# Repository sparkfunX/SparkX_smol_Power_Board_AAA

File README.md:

# SparkX smôl Power Board : AAA

[*SparkX smôl Power Board : AAA (SPX-18621)*](https://www.sparkfun.com/products/18621)

A power board for smôl:
- JST battery connector
- Boost converter
- Power can be provided by one or two AAA or AA batteries
- ATtiny43 for intelligent power management

## Repository Contents

- **/Documentation** - Datasheets etc.
- **/Hardware** - Eagle design files
- **LICENSE.md** contains the licence information

## Product Versions

- [SPX-18621](https://www.sparkfun.com/products/18621) - Original SparkX Release.

## License Information

This product is _**open source**_!

Please review the LICENSE.md file for license information.

If you have any questions or concerns on licensing, please contact technical support on our [SparkFun forums](https://forum.sparkfun.com/viewforum.php?f=123).

Distributed as-is; no warranty is given.

- Your friends at SparkFun.

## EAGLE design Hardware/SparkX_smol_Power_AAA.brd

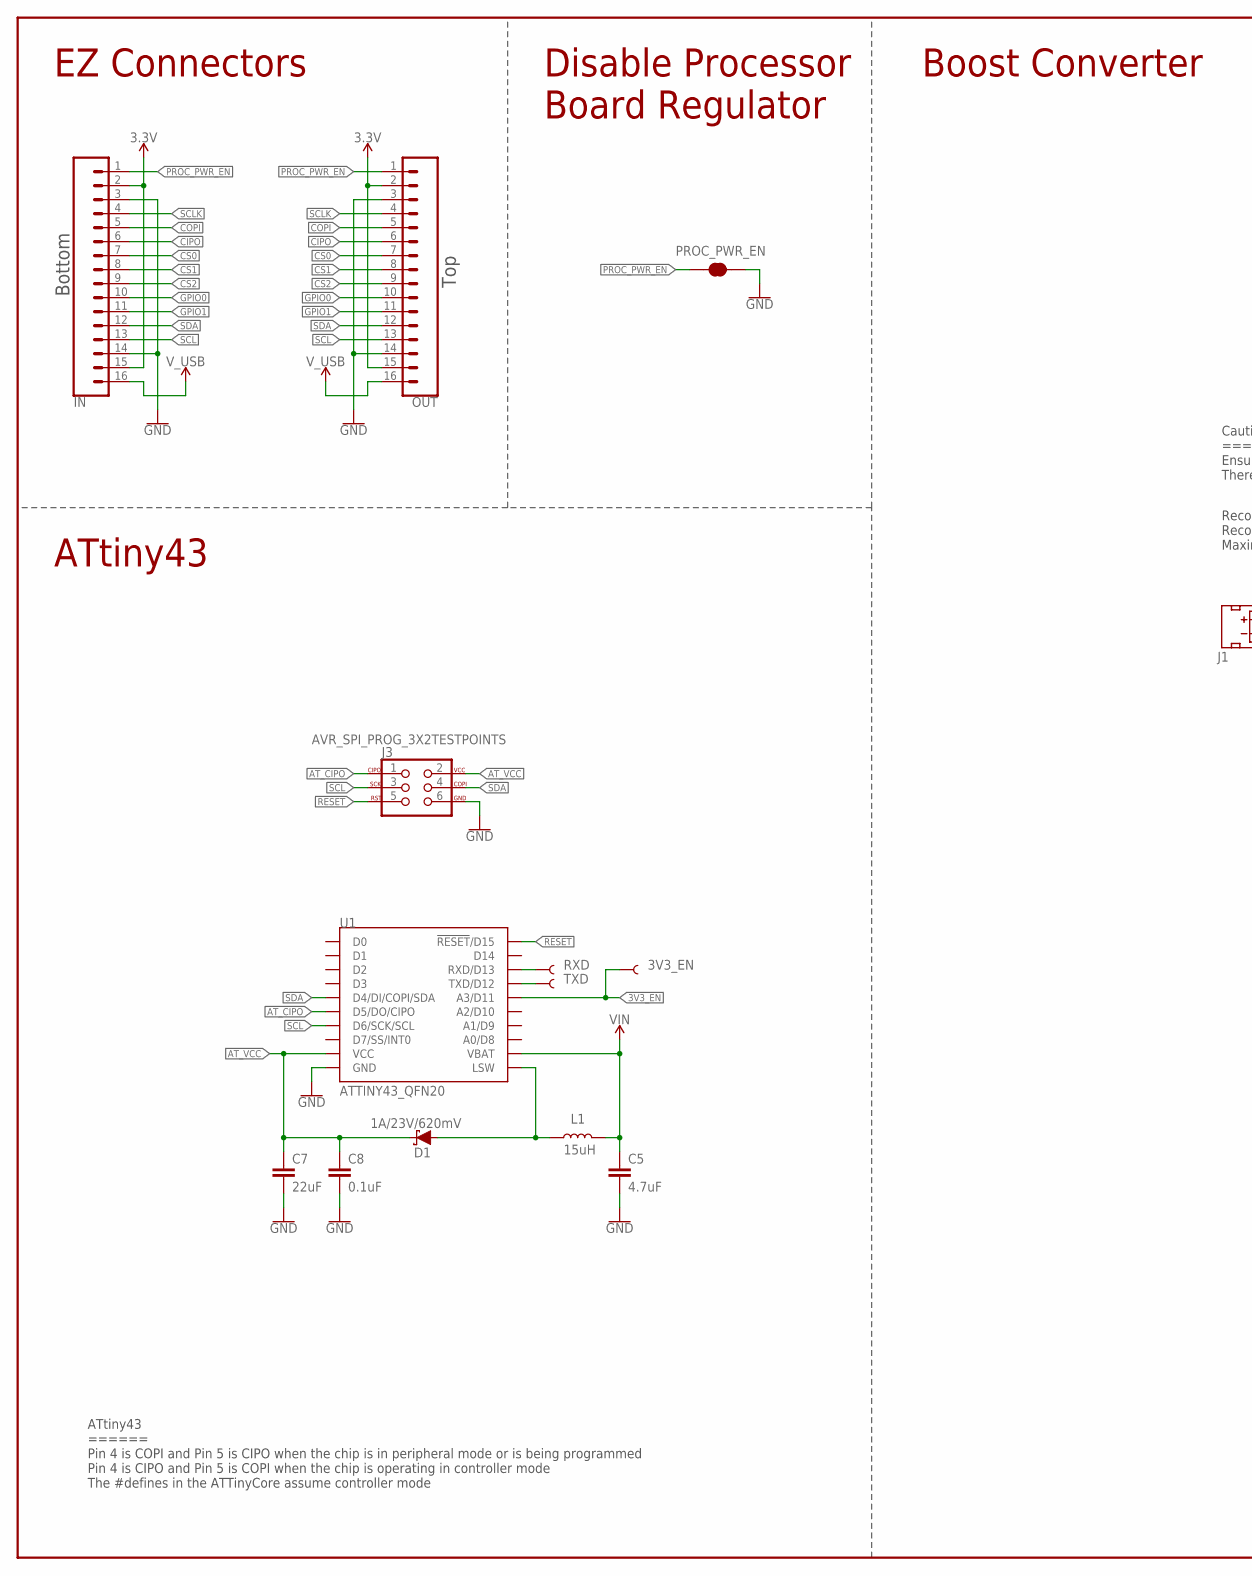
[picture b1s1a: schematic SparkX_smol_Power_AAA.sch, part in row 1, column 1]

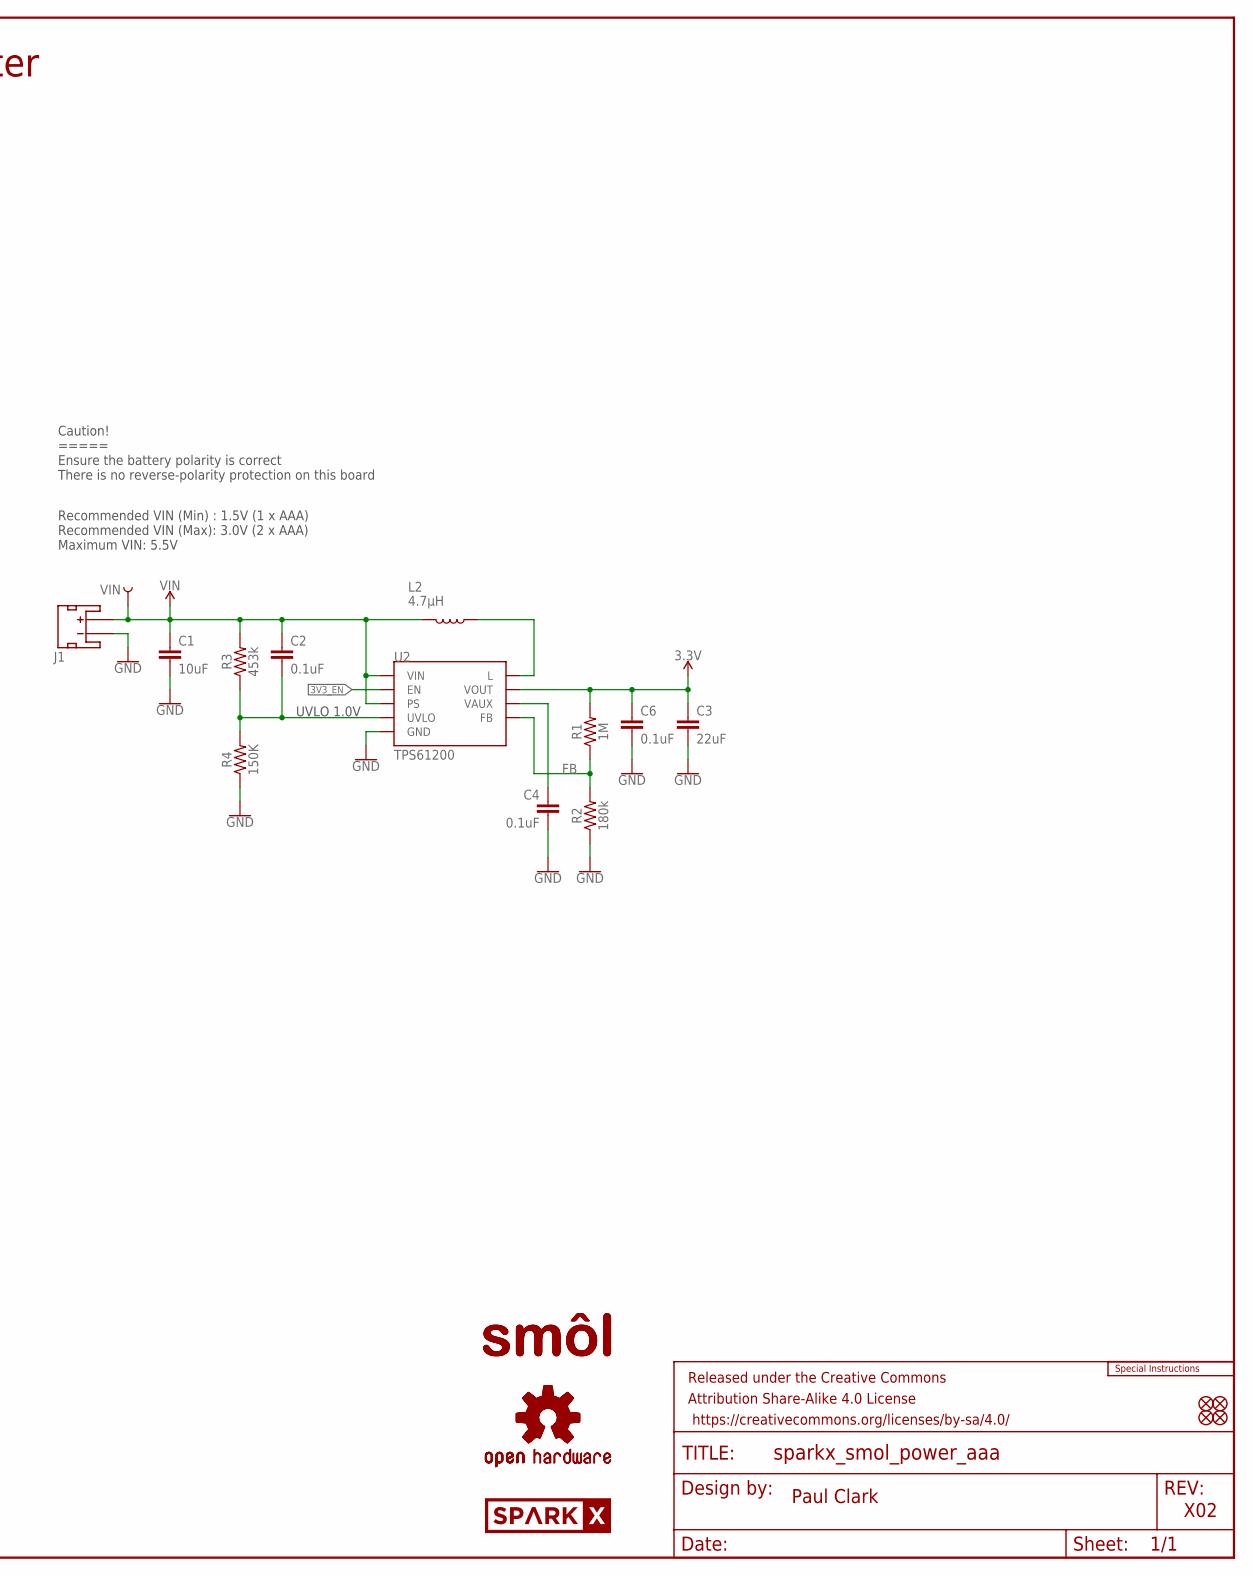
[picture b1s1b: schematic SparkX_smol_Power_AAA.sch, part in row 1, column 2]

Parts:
3V3_EN: TEST-POINT3X4; PAD.03X.04
C1: 10uF; 0402-TIGHT
C2, C4, C6, C8: 0.1uF; 0402-TIGHT
C3, C7: 22uF; 0603
C5: 4.7uF; 0402-TIGHT
D1: 1A/23V/620mV; SOD-323
FD1, FD2, FD3, FD4: FIDUCIALUFIDUCIAL; FIDUCIAL-MICRO
FRAME1: FRAME-LEDGER; CREATIVE_COMMONS
IN: CONN_16FPC_16_0.5MM; FPC_16_0.5MM
J1: JST_2MM_MALE; JST-2-SMD
J3: AVR_SPI_PROG_3X2TESTPOINTS; 2X3_TEST_POINTS
L1: 15uH; INDUCTOR_LQH32
L2: 4.7μH; INDUCTOR_4X4MM
LOGO1: SPECIAL_INSTRUCTIONS-ORDERING; ORDERING_INSTRUCTIONS
LOGO2, LOGO3: OSHW-LOGOMINI; OSHW-LOGO-MINI
OUT: CONN_16FPC_16_0.5MM; FPC_16_0.5MM
PROC_PWR_EN: JUMPER-SMT_2_NC_TRACE_SILK; SMT-JUMPER_2_NC_TRACE_SILK
R1: 1M; 0402-TIGHT
R2: 180k; 0402-TIGHT
R3: 453k; 0402-TIGHT
R4: 150K; 0402-TIGHT
RXD: TEST-POINT3X4; PAD.03X.04
TXD: TEST-POINT3X4; PAD.03X.04
U1: ATTINY43_QFN20; QFN20_20M1
U2: TPS61200; QFN-10_PAD
U$1: SPARKX-LOGO3; SPARKX-SMALL
U$13, U$14: SMOL_LOGOSMALL; SMOL_SMALL
VIN: TEST-POINT3X4; PAD.03X.04

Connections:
3.3V: C3.1, C6.1, IN.2, IN.15, OUT.2, OUT.15, R1.2, U2.2 (VOUT)
3V3_EN: 3V3_EN.1, U1.14 (A3/D11), U2.6 (EN)
!RESET!: J3.5, U1.18 (!RESET!/D15)
AT_CIPO: J3.1, U1.4 (D5/DO/CIPO)
AT_VCC: C7.1, C8.1, D1.C, J3.2, U1.7 (VCC)
CIPO: IN.6, OUT.6
COPI: IN.5, OUT.5
CS0: IN.7, OUT.7
CS1: IN.8, OUT.8
CS2: IN.9, OUT.9
FB: R1.1, R2.2, U2.10 (FB)
GND: C1.2, C3.2, C4.2, C5.2, C6.2, C7.2, C8.2, IN.3, IN.14, J1.1 (-), J3.6, OUT.3, OUT.14, PROC_PWR_EN.2, R2.1, R4.1, U1.8 (GND), U1.PAD (GND), U2.4 (GND), U2.9 (GND), U2.11 (GND), U2.12 (GND), U2.13 (GND), U2.14 (GND), U2.15 (GND)
GPIO0: IN.10, OUT.10
GPIO1: IN.11, OUT.11
unnamed: L2.P$1 (1), U2.3 (L)
unnamed: D1.A, L1.P$1 (1), U1.9 (LSW)
unnamed: C4.1, U2.1 (VAUX)
PROC_PWR_EN: IN.1, OUT.1, PROC_PWR_EN.1
RXD: RXD.1, U1.16 (RXD/D13)
SCL: IN.13, J3.3, OUT.13, U1.5 (D6/SCK/SCL)
SCLK: IN.4, OUT.4
SDA: IN.12, J3.4, OUT.12, U1.3 (D4/DI/COPI/SDA)
TXD: TXD.1, U1.15 (TXD/D12)
UVLO: C2.2, R3.1, R4.2, U2.7 (UVLO)
VIN: C1.1, C2.1, C5.1, J1.2 (+), L1.P$2 (2), L2.P$2 (2), R3.2, U1.10 (VBAT), U2.5 (VIN), U2.8 (PS), VIN.1
V_USB: IN.16, OUT.16

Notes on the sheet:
Paul Clark
X02
EZ Connectors
Top
Bottom
Disable Processor Board Regulator
ATtiny43
ATtiny43 ====== Pin 4 is COPI and Pin 5 is CIPO when the chip is in peripheral mode or is being programmed Pin 4 is CIPO and Pin 5 is COPI when the chip is operating in controller mode The #defines in the ATTinyCore assume controller mode
UVLO 1.0V
Boost Converter
Recommended VIN (Min) : 1.5V (1 x AAA) Recommended VIN (Max): 3.0V (2 x AAA) Maximum VIN: 5.5V
Caution! ===== Ensure the battery polarity is correct There is no reverse-polarity protection on this board

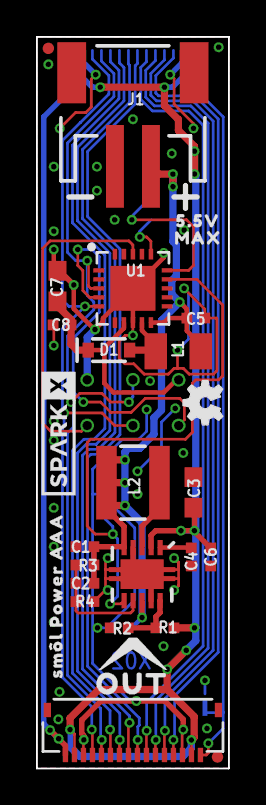
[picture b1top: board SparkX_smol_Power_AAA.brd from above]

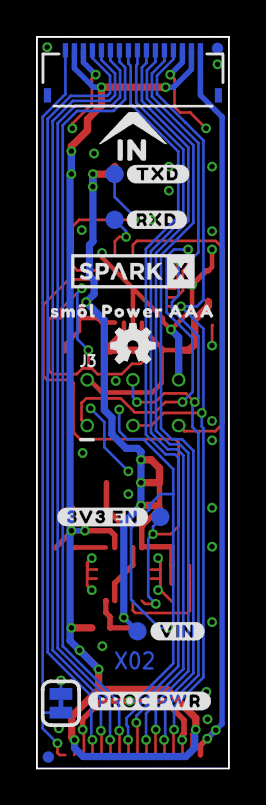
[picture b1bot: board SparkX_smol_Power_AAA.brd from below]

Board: 2 copper layers, 10.7 x 40.6 mm, 49 parts (19 on the bottom side), 26 nets.

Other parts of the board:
U$2, U$8: SM�L_POWER_AAA0
U$3: OUT0
U$4: #TXD#0
U$5: #VIN#0
U$6: #3V3_EN#0
U$7: #PROC_PWR#0
U$9: #RXD#0
U$10: 5#5V0
U$11: MAX0
U$12: IN0
U$20: SPARKX-LOGO3; SPARKX-SMALL

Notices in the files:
parts and their libraries:
SparkFun-Aesthetics: Licensing: Creative Commons ShareAlike 4.0 International - https://creativecommons.org/licenses/by-sa/4.0
SparkFun-Aesthetics: Released under the Creative Commons Attribution Share-Alike 4.0 License
SparkFun-Aesthetics: https://creativecommons.org/licenses/by-sa/4.0
